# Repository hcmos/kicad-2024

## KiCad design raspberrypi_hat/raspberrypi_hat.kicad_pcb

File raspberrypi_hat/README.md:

# ハードウェア
<br>
- 回路図  
<br>

# 端子
## CAN
### 使用したもの
- [MCP2515(コントローラ)](https://akizukidenshi.com/catalog/g/gI-12030/)
  CANプロトコルをSPIに変換するため．[外部クロック](https://akizukidenshi.com/catalog/g/gP-00147/)が必要(夢考房にあるやつ)
- [MCP2562FD(トランシーバ)](https://akizukidenshi.com/catalog/g/gI-14383/)
  物理層

### 起動ファイル
ラズパイOSでは`/boot/config.txt`．Ubuntuでは`/boot/firmware/config.txt`，同ディレクトリの`usercfg.txt`(推奨)に以下を追記．
```bash
# enable MCP2515
dtparam=spi=on
dtoverlay=mcp2515-can0,oscillator=20000000,interrupt=25
dtoverlay=spi-bcm2835
```
`oscillator=`は外部クロックに合わせる．`interrupt=`は配線したGPIOを指定．  
書き終わったらreboot!

#### 確認
```bash
$ dmesg | grep -e CAN -e can
[    -] CAN device driver interface
[    -] mcp251x spi0.0 can0: MCP2515 successfully initialized.
```
みたいに返ってくればOK．

### 有効化
デバイスの状態をUPにする．
```bash
sudo ip link set can0 type can bitrate 1000000
sudo ip link set can0 up
```
ビットレートは環境に合わせて変更．->`ifconifg`にCAN0が出てくるはず．

### 受信
CANパケットを[candump](http://manpages.ubuntu.com/manpages/bionic/man1/candump.1.html)で確認する．  
`candump can0 -x`  

```bash
can0  RX - -  000   [8]  00 00 00 00 00 00 00 00
```
などと表示されれば成功．

あとは`socketcan_if`などのパッケージでlinux-canで触ってみる．

## UART
GPIO14(TXD0), GPIO15(RXD0)とつなげただけ．  
GND | +5V | TX | RX

## I2C
GPIO2(SDA1), GPIO3(SDL1)とつなげただけ．  
GND | +5V | SDA | SCL

## GPIO24
制御緊急停止用．  
GND | GPIO24

## FAN
ファンコントロールのためのGPIO． ラズパイコンフィグから指定．  
GND | +5V | GPIO18

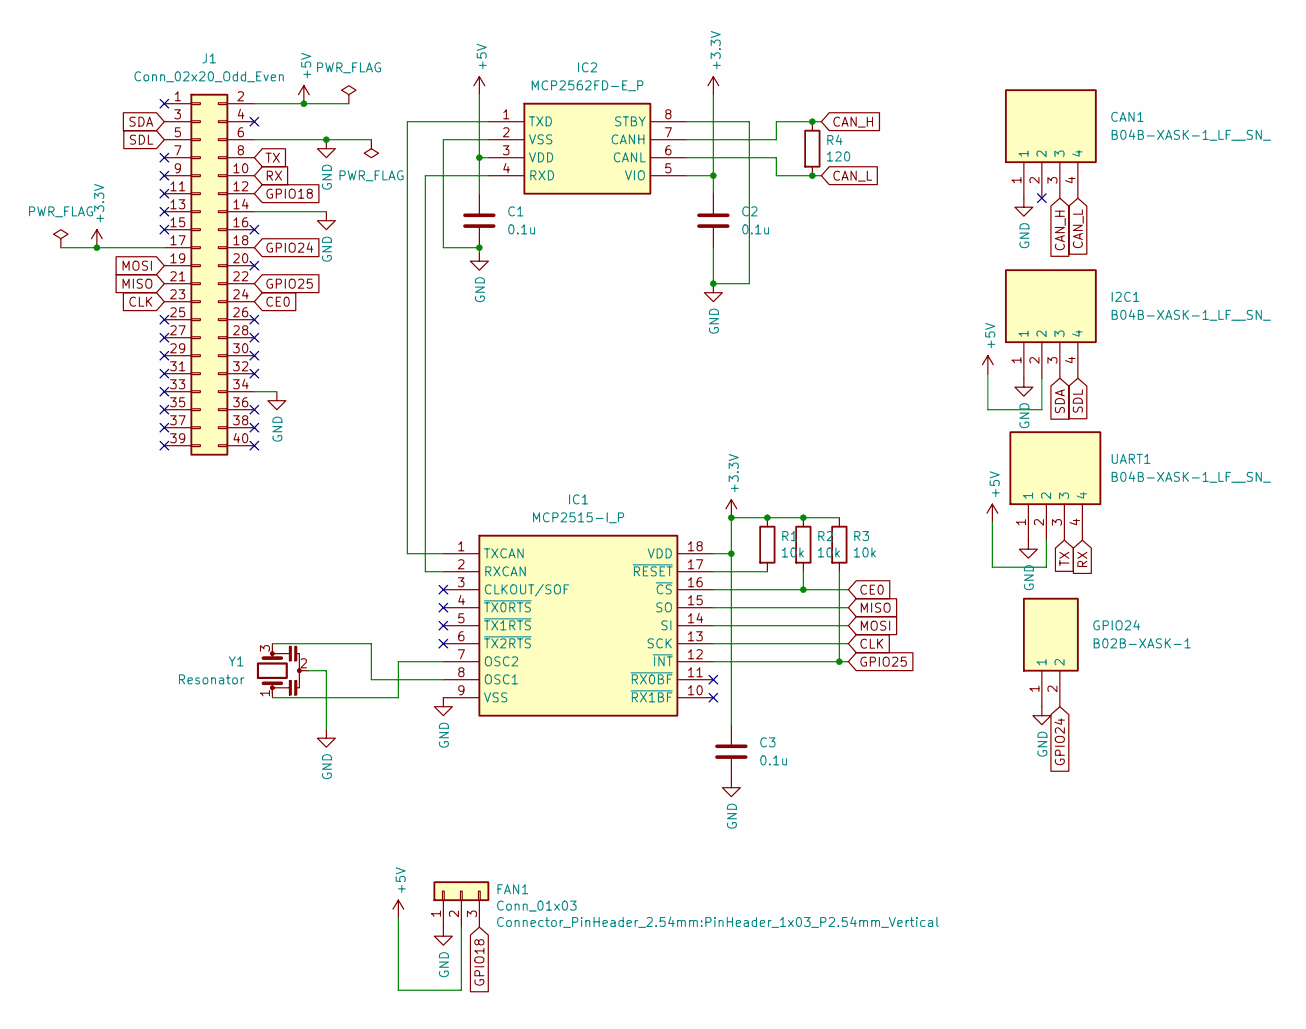
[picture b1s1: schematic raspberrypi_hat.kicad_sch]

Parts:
C1, C2, C3: 0.1u; C_0603_1608Metric_Pad1.08x0.95mm_HandSolder
CAN1: B04B-XASK-1_LF__SN_; SHDR4W60P0X250_1X4_1250X640X880P; Manufacturer_Part_Number B04B-XASK-1(LF)(SN)
FAN1: Conn_01x03; PinHeader_1x03_P2.54mm_Vertical
GPIO24: B02B-XASK-1; SHDR2W60P0X250_1X2_750X640X880P; Manufacturer_Part_Number B02B-XASK-1
I2C1: B04B-XASK-1_LF__SN_; SHDR4W60P0X250_1X4_1250X640X880P; Manufacturer_Part_Number B04B-XASK-1(LF)(SN)
IC1: MCP2515-I_P; DIP794W56P254L2286H533Q18N; Manufacturer_Part_Number MCP2515-I/P
IC2: MCP2562FD-E_P; DIP781W56P254L950H533Q8N; Manufacturer_Part_Number MCP2562FD-E/P
J1: Conn_02x20_Odd_Even; PinSocket_2x20_P2.54mm_Vertical
R1, R2, R3: 10k; R_0603_1608Metric_Pad0.98x0.95mm_HandSolder
R4: 120; R_0603_1608Metric_Pad0.98x0.95mm_HandSolder
UART1: B04B-XASK-1_LF__SN_; SHDR4W60P0X250_1X4_1250X640X880P; Manufacturer_Part_Number B04B-XASK-1(LF)(SN)
Y1: Resonator; Resonator_Murata_CSTLSxxxX-3Pin_W5.5mm_H3.0mm

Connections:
+3.3V: C2.1, C3.1, IC1.18 (VDD), IC2.5 (VIO), J1.17, R1.1, R2.1, R3.1
+5V: C1.1, FAN1.2, I2C1.2, IC2.3 (VDD), J1.2, UART1.2
CAN_H: CAN1.3, IC2.7 (CANH), R4.1
CAN_L: CAN1.4, IC2.6 (CANL), R4.2
CE0: IC1.16 (~CS), J1.24, R2.2
CLK: IC1.13 (SCK), J1.23
GND: C1.2, C2.2, C3.2, CAN1.1, FAN1.1, GPIO24.1, I2C1.1, IC1.9 (VSS), IC2.2 (VSS), IC2.8 (STBY), J1.6, J1.14, J1.34, UART1.1, Y1.2
GPIO18: FAN1.3, J1.12
GPIO24: GPIO24.2, J1.18
GPIO25: IC1.12 (~INT), J1.22, R3.2
MISO: IC1.15 (SO), J1.21
MOSI: IC1.14 (SI), J1.19
unnamed: IC1.8 (OSC1), Y1.3
unnamed: IC1.7 (OSC2), Y1.1
unnamed: IC1.2 (RXCAN), IC2.4 (RXD)
unnamed: IC1.1 (TXCAN), IC2.1 (TXD)
unnamed: IC1.17 (~RESET), R1.2
RX: J1.10, UART1.4
SDA: I2C1.3, J1.3
SDL: I2C1.4, J1.5
TX: J1.8, UART1.3

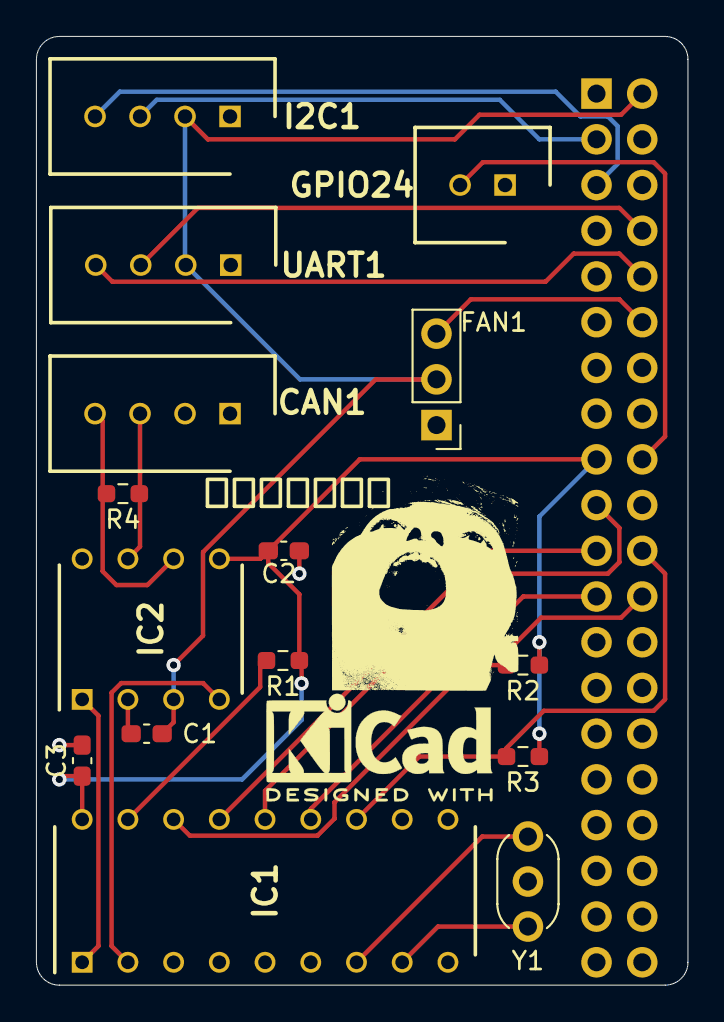
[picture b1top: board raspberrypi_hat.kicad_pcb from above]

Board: 2 copper layers, 36.2 x 52.7 mm, 16 parts (1 on the bottom side), 21 nets.

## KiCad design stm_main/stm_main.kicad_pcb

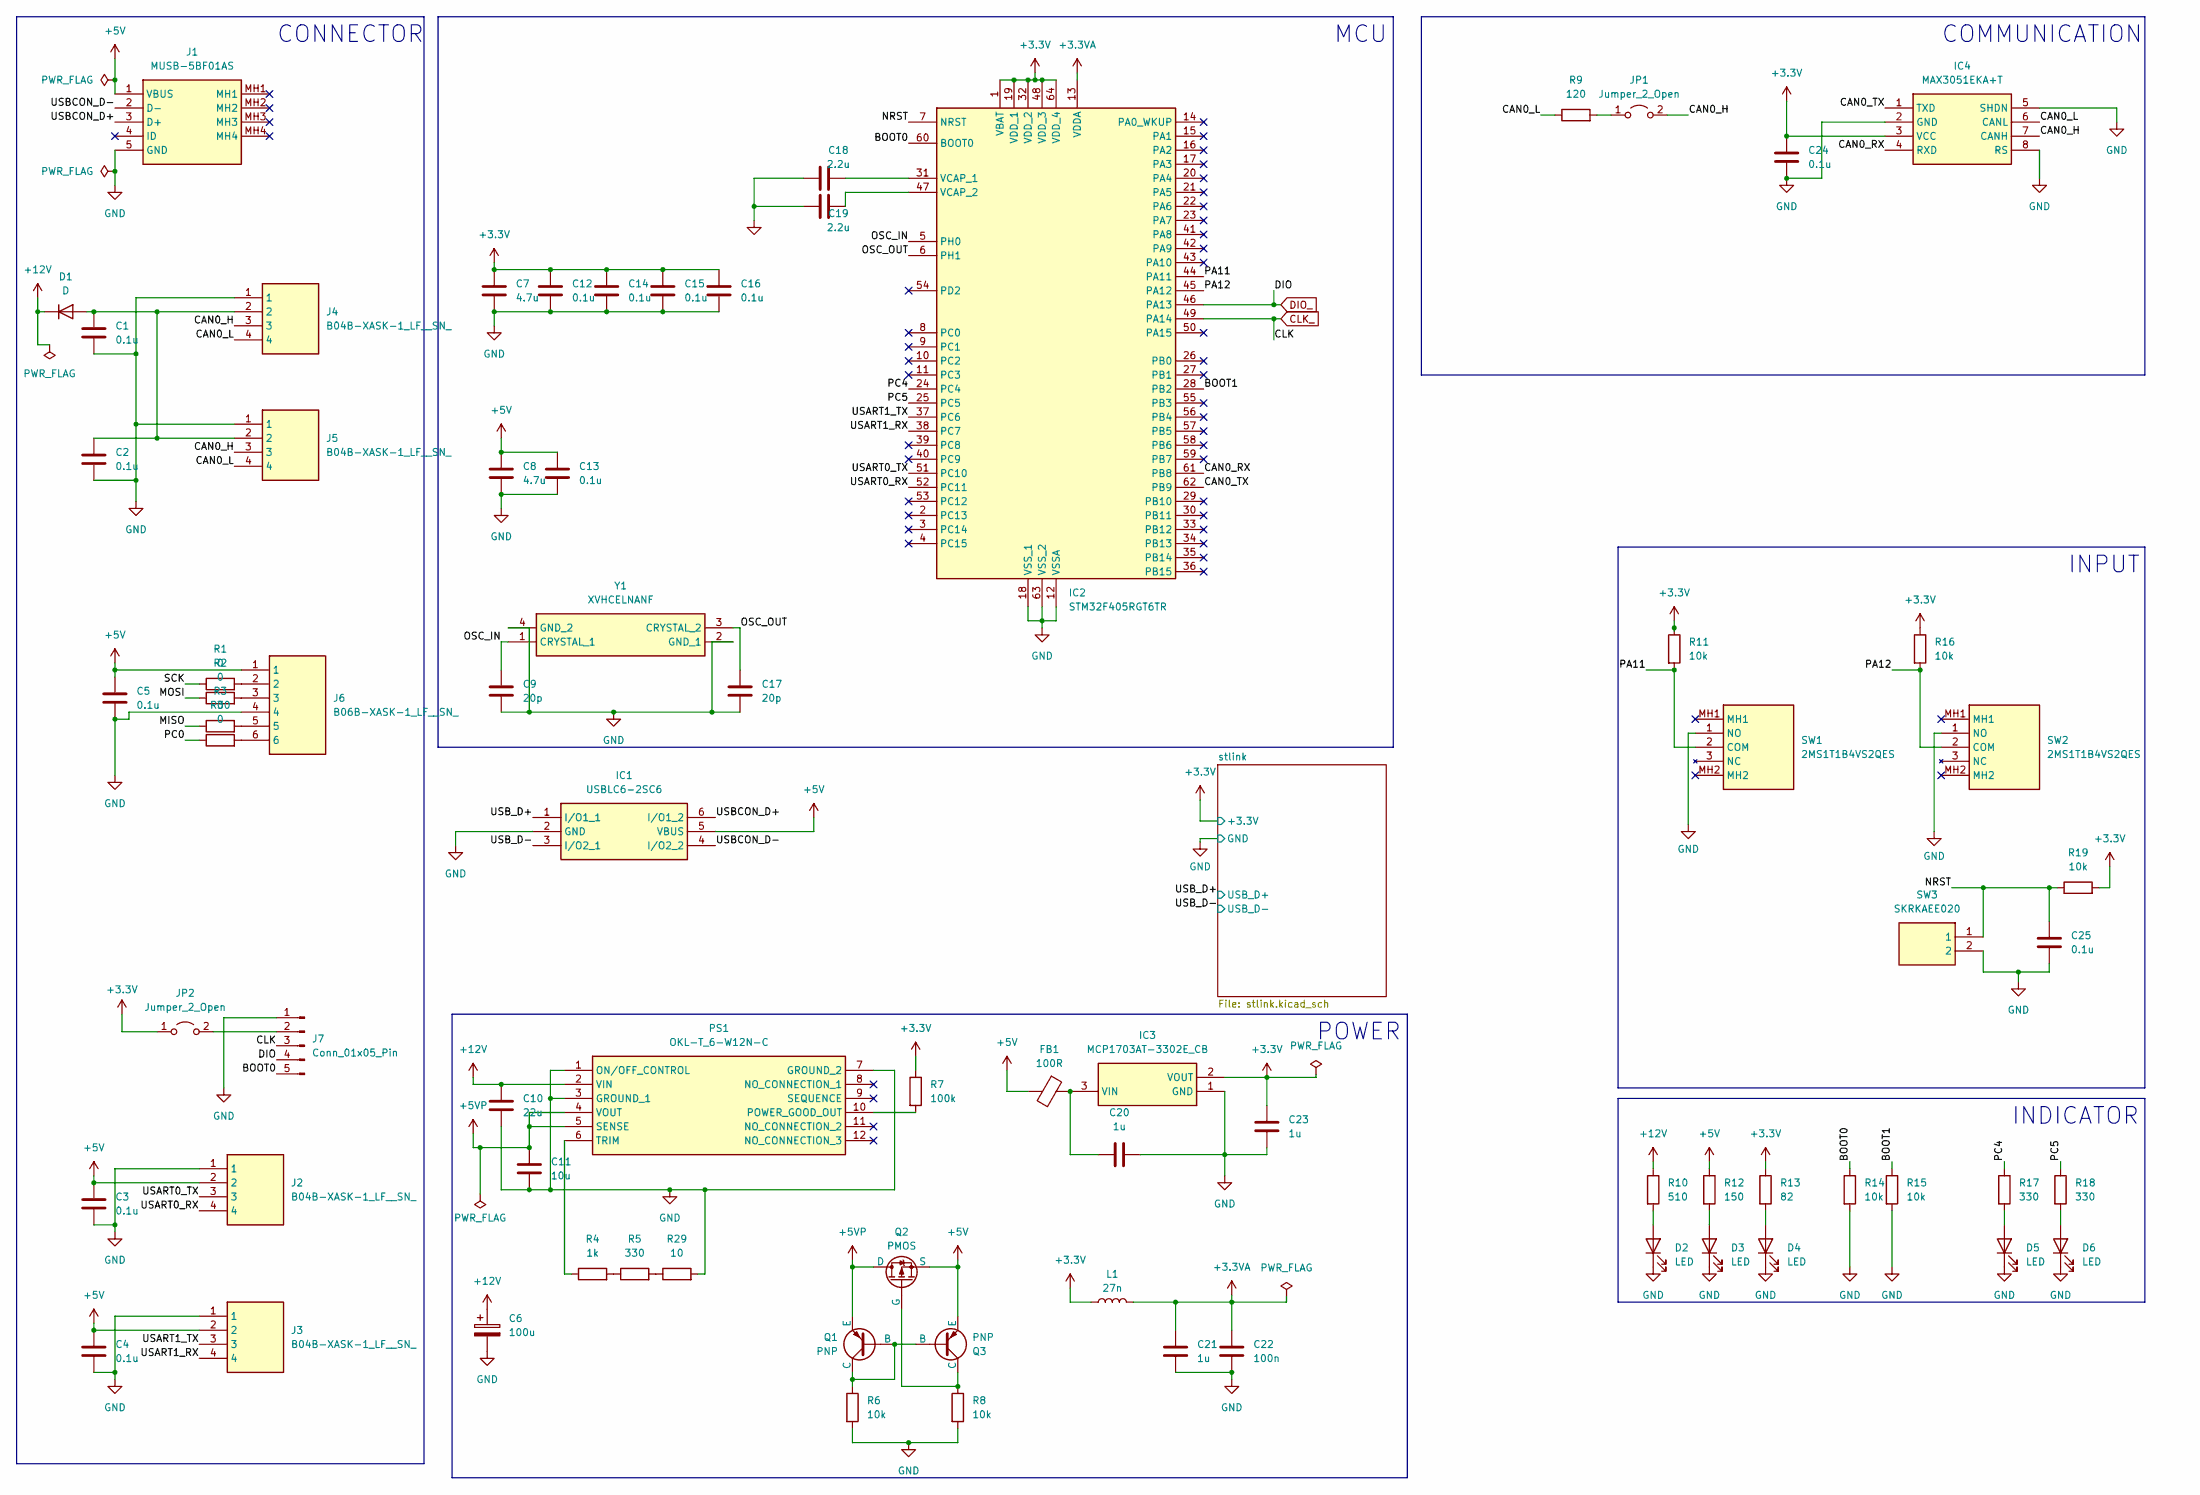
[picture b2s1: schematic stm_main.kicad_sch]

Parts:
C1, C2, C3, C4, C5, C12, C13, C14, C15, C16, C24, C25: 0.1u; C_0603_1608Metric
C6: 100u; CP_Radial_D5.0mm_P2.00mm
C7, C8: 4.7u; C_0603_1608Metric
C9, C17: 20p; C_0603_1608Metric
C10: 22u; C_0603_1608Metric
C11: 10u; C_0603_1608Metric
C18, C19: 2.2u; C_0603_1608Metric
C20, C21, C23: 1u; C_0603_1608Metric
C22: 100n; C_0603_1608Metric
D1: D; D_0603_1608Metric
D2, D3, D4, D5, D6: LED; D_0603_1608Metric
FB1: 100R; R_0603_1608Metric
IC1: USBLC6-2SC6; Manufacturer_Part_Number USBLC6-2SC6
IC2: STM32F405RGT6TR; Manufacturer_Part_Number STM32F405RGT6TR
IC3: MCP1703AT-3302E_CB; Manufacturer_Part_Number MCP1703AT-3302E/CB
IC4: MAX3051EKA+T; Manufacturer_Part_Number MAX3051EKA+T
J1: MUSB-5BF01AS; MUSB5BF01AS; Manufacturer_Part_Number MUSB-5BF01AS
J2, J3, J4, J5: B04B-XASK-1_LF__SN_; SHDR4W60P0X250_1X4_1250X640X880P; Manufacturer_Part_Number B04B-XASK-1(LF)(SN)
J6: B06B-XASK-1_LF__SN_; SHDR6W80P0X250_1X6_1750X640X880P; Manufacturer_Part_Number B06B-XASK-1(LF)(SN)
J7: Conn_01x05_Pin; PinHeader_1x05_P2.54mm_Vertical
JP1, JP2: Jumper_2_Open; PinHeader_1x02_P2.54mm_Vertical
L1: 27n; L_0603_1608Metric
PS1: OKL-T_6-W12N-C; OKLT6W12NC; Manufacturer_Part_Number OKL-T/6-W12N-C
Q1, Q3: PNP; MMBT3906WT1G
Q2: PMOS; SSM3J332RLFT
R1, R2, R3, R30: 0; R_0603_1608Metric
R4: 1k; R_0603_1608Metric
R5, R17, R18: 330; R_0603_1608Metric
R6, R8, R11, R14, R15, R16, R19: 10k; R_0603_1608Metric
R7: 100k; R_0603_1608Metric
R9: 120; R_0603_1608Metric
R10: 510; R_0603_1608Metric
R12: 150; R_0603_1608Metric
R13: 82; R_0603_1608Metric
R29: 10; R_0603_1608Metric
SW1, SW2: 2MS1T1B4VS2QES; Manufacturer_Part_Number 2MS1T1B4VS2QES
SW3: SKRKAEE020; Manufacturer_Part_Number SKRKAEE020
Y1: XVHCELNANF; Manufacturer_Part_Number XVHCELNANF

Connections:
+3.3V: C7.1, C12.1, C14.1, C15.1, C16.1, C23.2, C24.1, IC2.1 (VBAT), IC2.19 (VDD_1), IC2.32 (VDD_2), IC2.48 (VDD_3), IC2.64 (VDD_4), IC3.2 (VOUT), IC4.3 (VCC), JP2.1 (A), L1.1, R7.1, R11.1, R13.1, R16.1, R19.2; also elsewhere on the board
+3.3VA: C21.2, C22.2, IC2.13 (VDDA), L1.2
+5V: C3.1, C4.1, C5.1, C8.1, C13.1, FB1.2, IC1.5 (VBUS), J1.1 (VBUS), J2.2, J3.2, J6.1, Q2.3 (S), Q3.3 (E), R12.1
+5VP: C11.1, PS1.4 (VOUT), PS1.5 (SENSE), Q1.3 (E), Q2.1 (D)
+12V: C6.1, C10.1, D1.1 (K), PS1.2 (VIN), R10.1
/BOOT1: IC2.28 (PB2), R15.1
/CAN0_H: IC4.7 (CANH), J4.3, J5.3, JP1.2 (B)
/CAN0_L: IC4.6 (CANL), J4.4, J5.4, R9.1
/CAN0_RX: IC2.61 (PB8), IC4.4 (RXD)
/CAN0_TX: IC2.62 (PB9), IC4.1 (TXD)
/MISO: R3.1
/MOSI: R2.1
/NRST: C25.1, IC2.7 (NRST), R19.1, SW3.1
/OSC_IN: C9.1, IC2.5 (PH0), Y1.1 (CRYSTAL_1)
/OSC_OUT: C17.1, IC2.6 (PH1), Y1.3 (CRYSTAL_2)
/PA11: IC2.44 (PA11), R11.2, SW1.2 (COM)
/PA12: IC2.45 (PA12), R16.2, SW2.2 (COM)
/PC0: R30.1
/PC4: IC2.24 (PC4), R17.1
/PC5: IC2.25 (PC5), R18.1
/SCK: R1.1
/USART0_RX: IC2.52 (PC11), J2.4
/USART0_TX: IC2.51 (PC10), J2.3
/USART1_RX: IC2.38 (PC7), J3.4
/USART1_TX: IC2.37 (PC6), J3.3
/USBCON_D+: IC1.6 (I/O1_2), J1.3 (D+)
/USBCON_D-: IC1.4 (I/O2_2), J1.2 (D-)
/USB_D+: IC1.1 (I/O1_1); also elsewhere on the board
/USB_D-: IC1.3 (I/O2_1); also elsewhere on the board
GND: C1.1, C2.2, C3.2, C4.2, C5.2, C6.2, C7.2, C8.2, C9.2, C10.2, C11.2, C12.2, C13.2, C14.2, C15.2, C16.2, C17.2, C18.1, C19.1, C20.2, C21.1, C22.1, C23.1, C24.2, C25.2, D2.1 (K), D3.1 (K), D4.1 (K), D5.1 (K), D6.1 (K), IC1.2 (GND), IC2.12 (VSSA), IC2.18 (VSS_1), IC2.63 (VSS_2), IC3.1 (GND), IC4.2 (GND), IC4.5 (SHDN), IC4.8 (RS), J1.5 (GND), J2.1, J3.1, J4.1, J5.1, J6.4, J7.1, PS1.1 (ON/OFF_CONTROL), PS1.3 (GROUND_1), PS1.7 (GROUND_2), R6.2, R8.2, R14.2, R15.2, R29.2, SW1.1 (NO), SW2.1 (NO), SW3.2, Y1.2 (GND_1), Y1.4 (GND_2); also elsewhere on the board
unnamed: C1.2, C2.1, D1.2 (A), J4.2, J5.2
unnamed: D2.2 (A), R10.2
unnamed: D3.2 (A), R12.2
unnamed: D4.2 (A), R13.2
unnamed: D5.2 (A), R17.2
unnamed: D6.2 (A), R18.2
unnamed: C18.2, IC2.31 (VCAP_1)
unnamed: C19.2, IC2.47 (VCAP_2)
unnamed: C20.1, FB1.1, IC3.3 (VIN)
unnamed: J6.2, R1.2
unnamed: J6.3, R2.2
unnamed: J6.5, R3.2
unnamed: J6.6, R30.2
unnamed: J7.2, JP2.2 (B)
unnamed: JP1.1 (A), R9.2
unnamed: PS1.10 (POWER_GOOD_OUT), R7.2
unnamed: PS1.6 (TRIM), R4.1
unnamed: Q1.1 (C), Q1.2 (B), Q3.2 (B), R6.1
unnamed: Q2.2 (G), Q3.1 (C), R8.1
unnamed: R4.2, R5.1
unnamed: R5.2, R29.1

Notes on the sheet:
MCU
COMMUNICATION
CONNECTOR
INDICATOR
INPUT
POWER

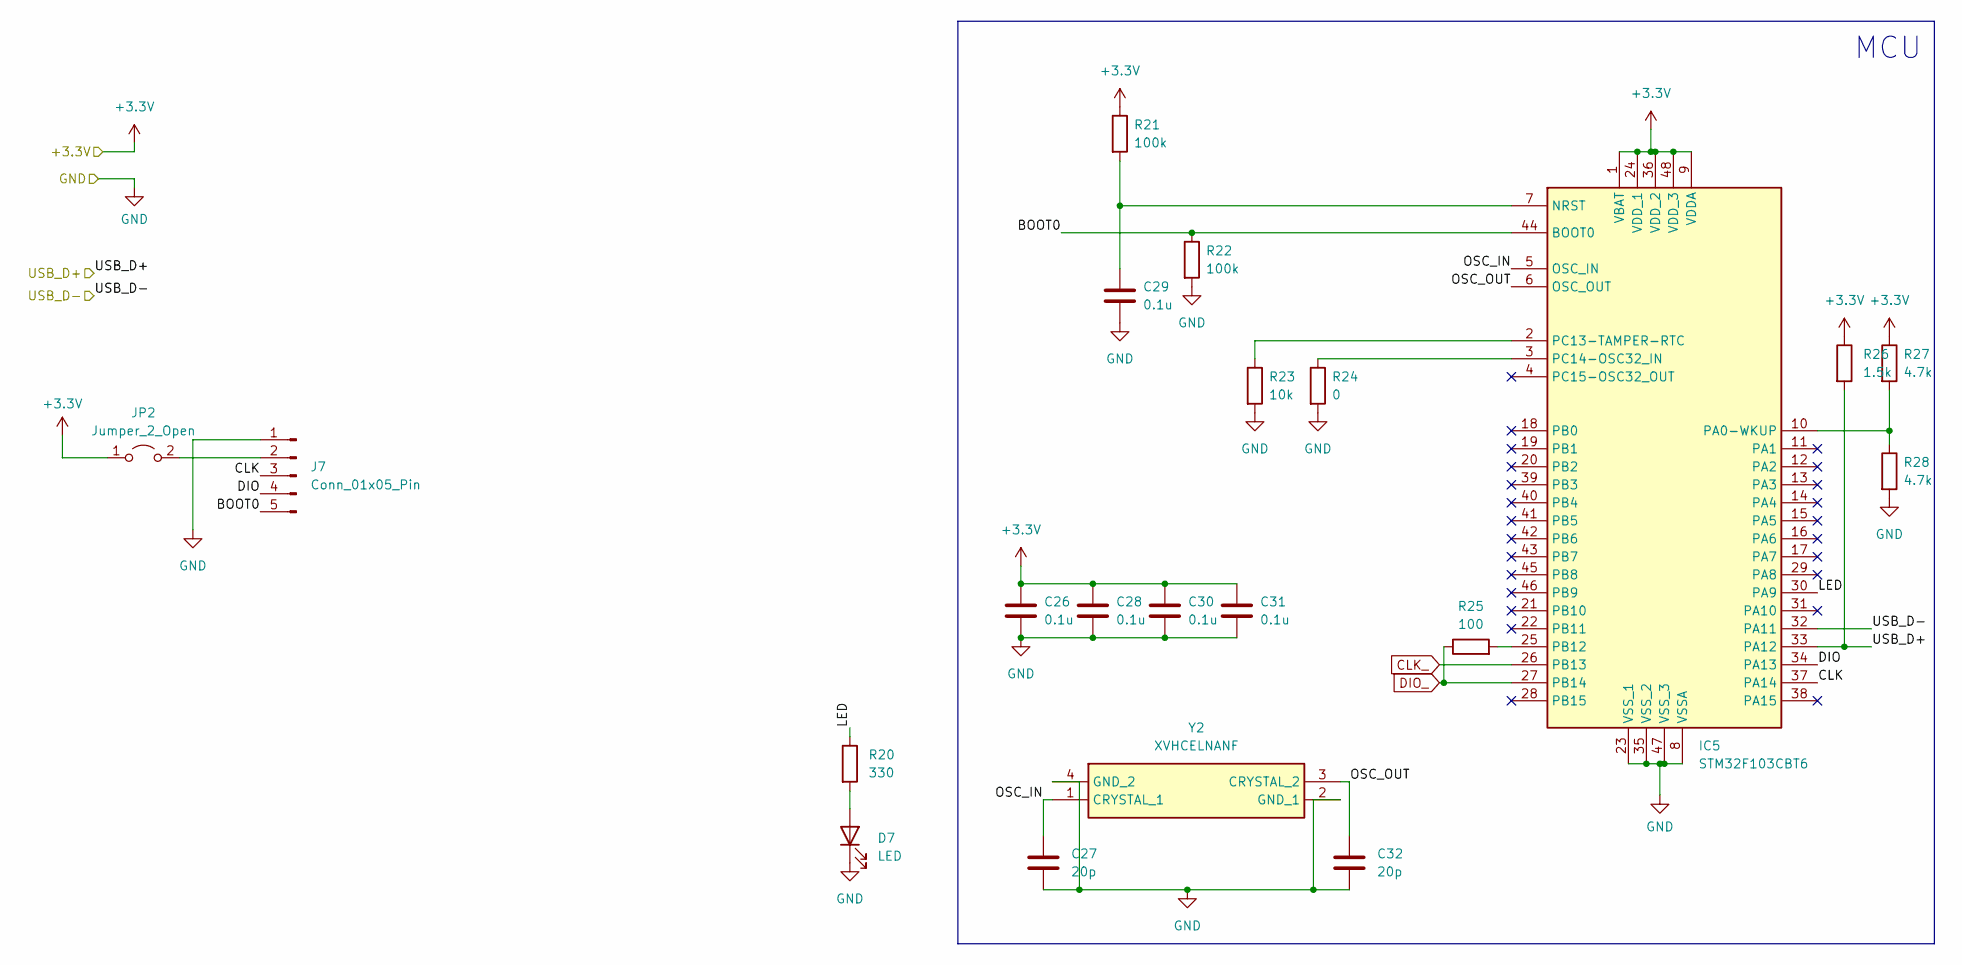
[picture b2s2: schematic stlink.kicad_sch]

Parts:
C26, C28, C29, C30, C31: 0.1u; C_0603_1608Metric
C27, C32: 20p; C_0603_1608Metric
D7: LED; D_0603_1608Metric
IC5: STM32F103CBT6; Manufacturer_Part_Number STM32F103CBT6
J7: Conn_01x05_Pin; PinHeader_1x05_P2.54mm_Vertical
JP2: Jumper_2_Open; PinHeader_1x02_P2.54mm_Vertical
R20: 330; R_0603_1608Metric
R21, R22: 100k; R_0603_1608Metric
R23: 10k; R_0603_1608Metric
R24: 0; R_0603_1608Metric
R25: 100; R_0603_1608Metric
R26: 1.5k; R_0603_1608Metric
R27, R28: 4.7k; R_0603_1608Metric
Y2: XVHCELNANF; Manufacturer_Part_Number XVHCELNANF

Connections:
+3.3V: C26.1, C28.1, C30.1, C31.1, IC5.1 (VBAT), IC5.9 (VDDA), IC5.24 (VDD_1), IC5.36 (VDD_2), IC5.48 (VDD_3), JP2.1 (A), R21.1, R26.1, R27.1; also elsewhere on the board
/USB_D+: IC5.33 (PA12), R26.2; also elsewhere on the board
/USB_D-: IC5.32 (PA11); also elsewhere on the board
/stlink/LED: IC5.30 (PA9), R20.1
/stlink/OSC_IN: C27.1, IC5.5 (OSC_IN), Y2.1 (CRYSTAL_1)
/stlink/OSC_OUT: C32.1, IC5.6 (OSC_OUT), Y2.3 (CRYSTAL_2)
GND: C26.2, C27.2, C28.2, C29.2, C30.2, C31.2, C32.2, D7.1 (K), IC5.8 (VSSA), IC5.23 (VSS_1), IC5.35 (VSS_2), IC5.47 (VSS_3), J7.1, R22.2, R23.2, R24.2, R28.2, Y2.2 (GND_1), Y2.4 (GND_2); also elsewhere on the board
unnamed: D7.2 (A), R20.2
unnamed: C29.1, IC5.7 (NRST), R21.2
unnamed: IC5.10 (PA0-WKUP), R27.2, R28.1
unnamed: IC5.25 (PB12), R25.2
unnamed: IC5.2 (PC13-TAMPER-RTC), R23.1
unnamed: IC5.3 (PC14-OSC32_IN), R24.1
unnamed: J7.2, JP2.2 (B)

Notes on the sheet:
MCU

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
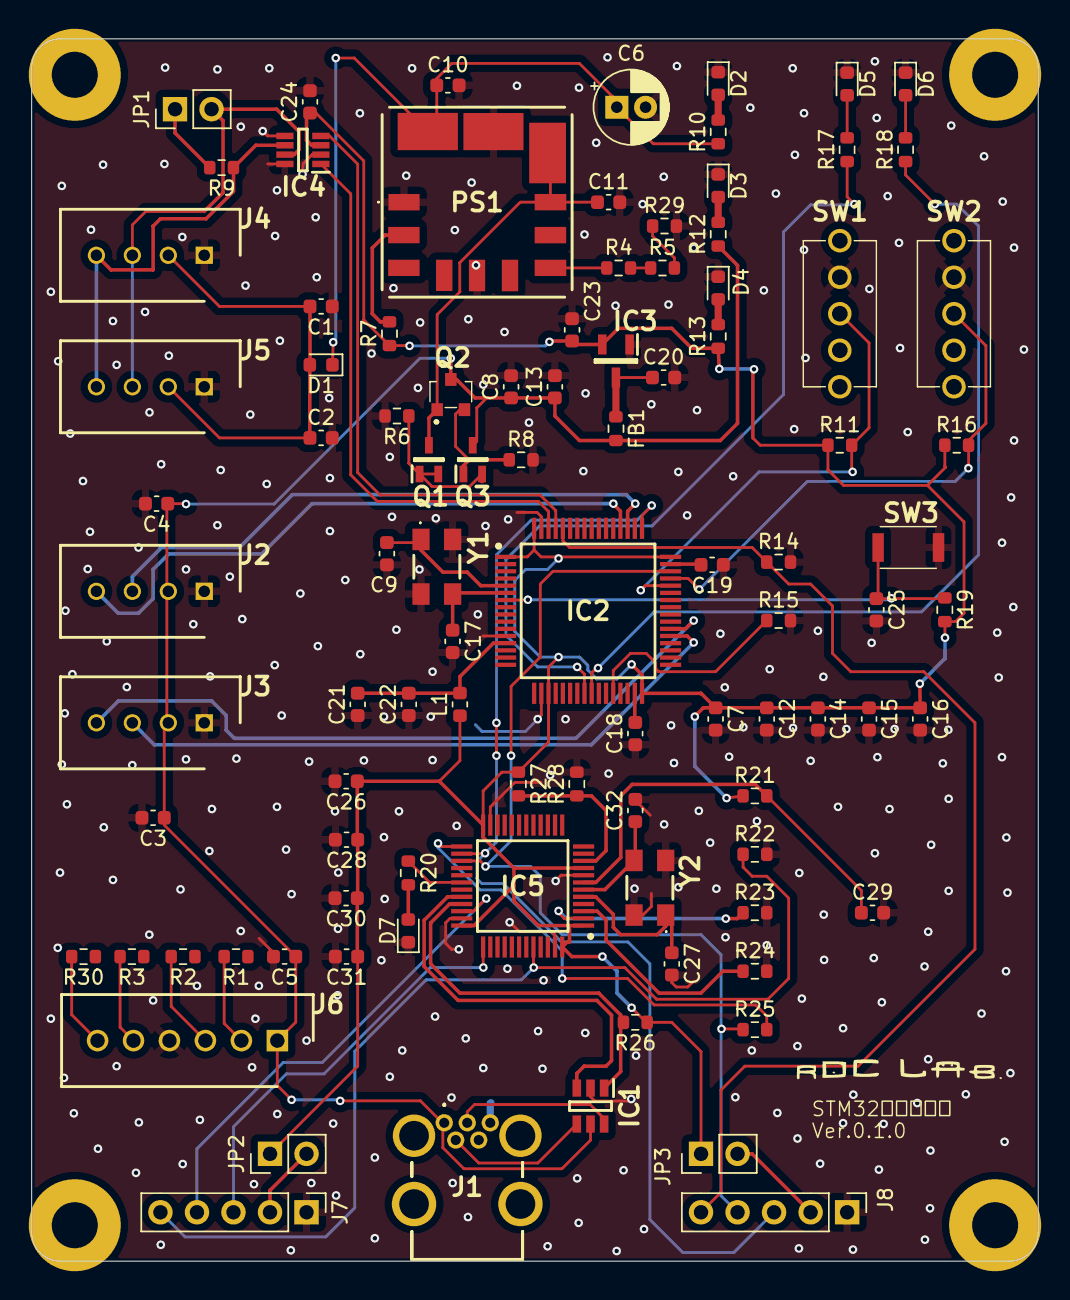
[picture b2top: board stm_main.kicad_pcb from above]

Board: 2 copper layers, 70.0 x 85.0 mm, 96 parts (0 on the bottom side), 63 nets.

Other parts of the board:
J8: Conn_01x05_Pin; PinHeader_1x05_P2.54mm_Vertical
JP3: Jumper_2_Open; PinHeader_1x02_P2.54mm_Vertical

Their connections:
+3.3V: JP3.1 (A); also elsewhere on the board
GND: J8.1; also elsewhere on the board
unnamed: J8.2, JP3.2 (B)

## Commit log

2024-08-05 ✨feat:first ci
2024-08-05 ✨feat:submodule
2024-09-18 ✨feat:発注8/27
2024-10-02 ✨feat:raspberrypi hat
2024-10-09 ✨feat:シルク
2024-10-14 🍰chore:sch
